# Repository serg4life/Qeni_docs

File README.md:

# Qeni — ESP32-S3 Wearable
Qeni is a custom wearable device based on the ESP32-S3,
designed and developed as a complete electronic product.

The project covers the complete hardware development process,
from system architecture and component selection to PCB and
mechanical design, manufacturing and validation.

## Manufactured prototype

## System Architecture

### High level organization

### Power management

### ESP32 and QSPI memory

### Peripherals

Brief explanation of the main subsystems...

## The PCB design
The PCB design has 4 layers in order to have enough grounding, layer 2 and 3 are solid ground planes. The stack up has been modified to meet the assembler requiremts as well as a proper width and spacing for differential traces. 

### Considerations
- The type and size of the vias have been chosed for a cheap manufacturing
- Components without Pb have been selected in order to meet EU requirements and RoHS
- Most components have been placed on top side for mechanic reasons
- QSPI and SPI traces need controlled length to meet timing requirements
- USB-C and RF traces are impedance-controlled through their width and spacing
- Layers 2 and 3 provide return paths for high-speed signals, reducing unwanted emissions and crosstalk between adjacent traces
- Ground vias are placed near high-speed signal vias to maintain a continuous return path when signals transition between layers

### Layer 1

### Layer 2

### Layer 3

### Layer 4

### PCB renders

## Main Components

- ESP32-S3
- AMOLED display
- Touch controller
- Switch
- IMU
- Speaker
- Microphone
- Audio driver
- Li-Po battery management ICs
- Power management ICs (charging and safety)

### Component Selection

Components were selected considering:

- Electrical requirements
- Availability and lifecycle
- Cost
- Package constraints
- Manufacturing requirements
- Applicable certifications/regulations
- Available support for software development

## Technologies

`ESP32-S3` `ESP-IDF` `C` `KiCad` `Fusion 360` `PCB Design`
`Embedded Systems` `Electronics` `Hardware Validation`

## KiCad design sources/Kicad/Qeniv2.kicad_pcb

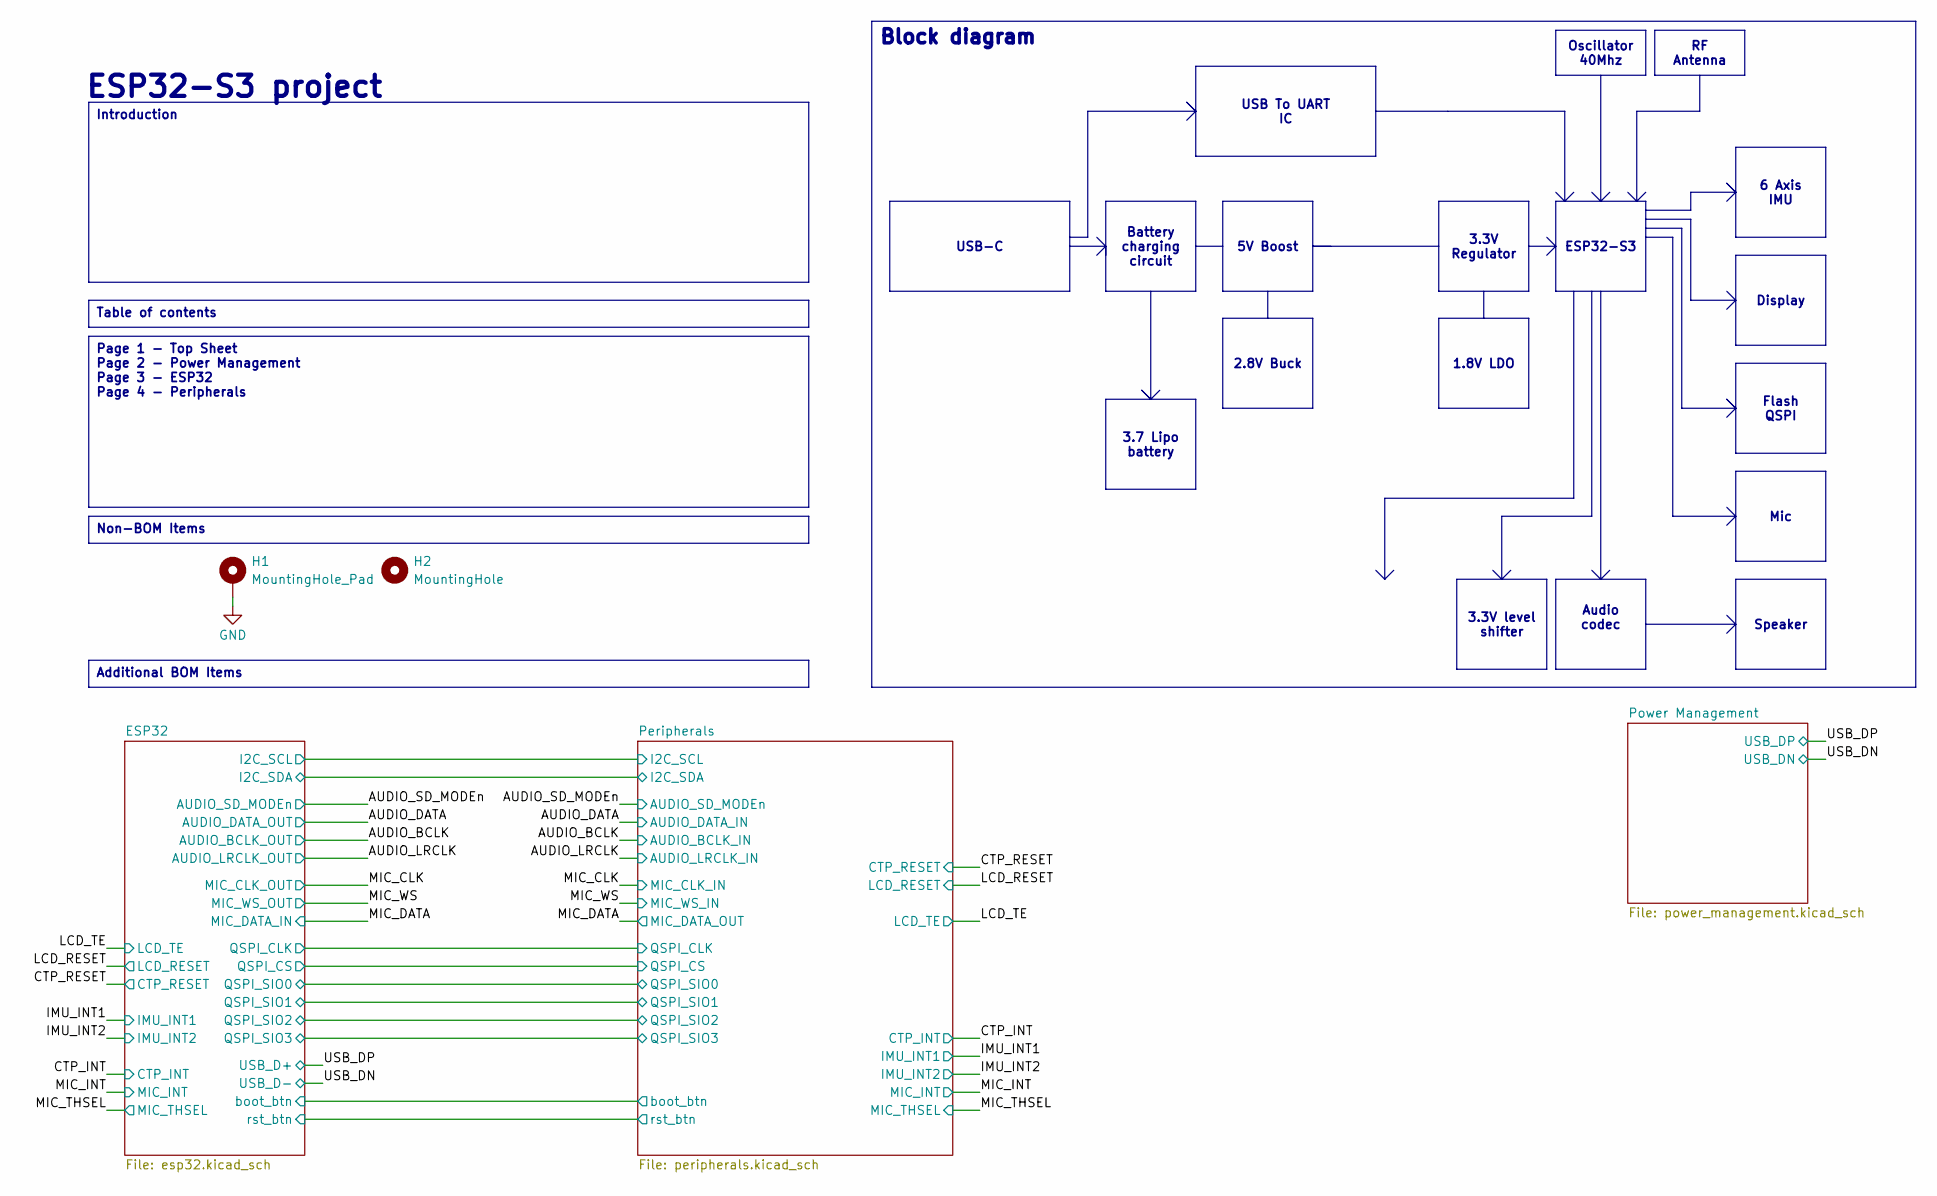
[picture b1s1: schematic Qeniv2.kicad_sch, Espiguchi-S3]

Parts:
H1: MountingHole_Pad; MountingHole_2.2mm_M2_ISO14580_Pad
H2: MountingHole; MountingHole_2.2mm_M2_ISO7380

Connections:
GND: H1.1; also elsewhere on the board

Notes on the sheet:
ESP32-S3 project
3.3V level shifter
RF Antenna
2.8V Buck
Additional BOM Items
Display
USB-C
6 Axis IMU
Battery charging circuit
Block diagram
Page 1 - Top Sheet Page 2 - Power Management Page 3 - ESP32 Page 4 - Peripherals
Table of contents
Introduction
Mic
1.8V LDO
ESP32-S3
Oscillator 40Mhz
5V Boost
3.3V Regulator
USB To UART IC
Audio codec
3.7 Lipo battery
Non-BOM Items
Flash QSPI
Speaker

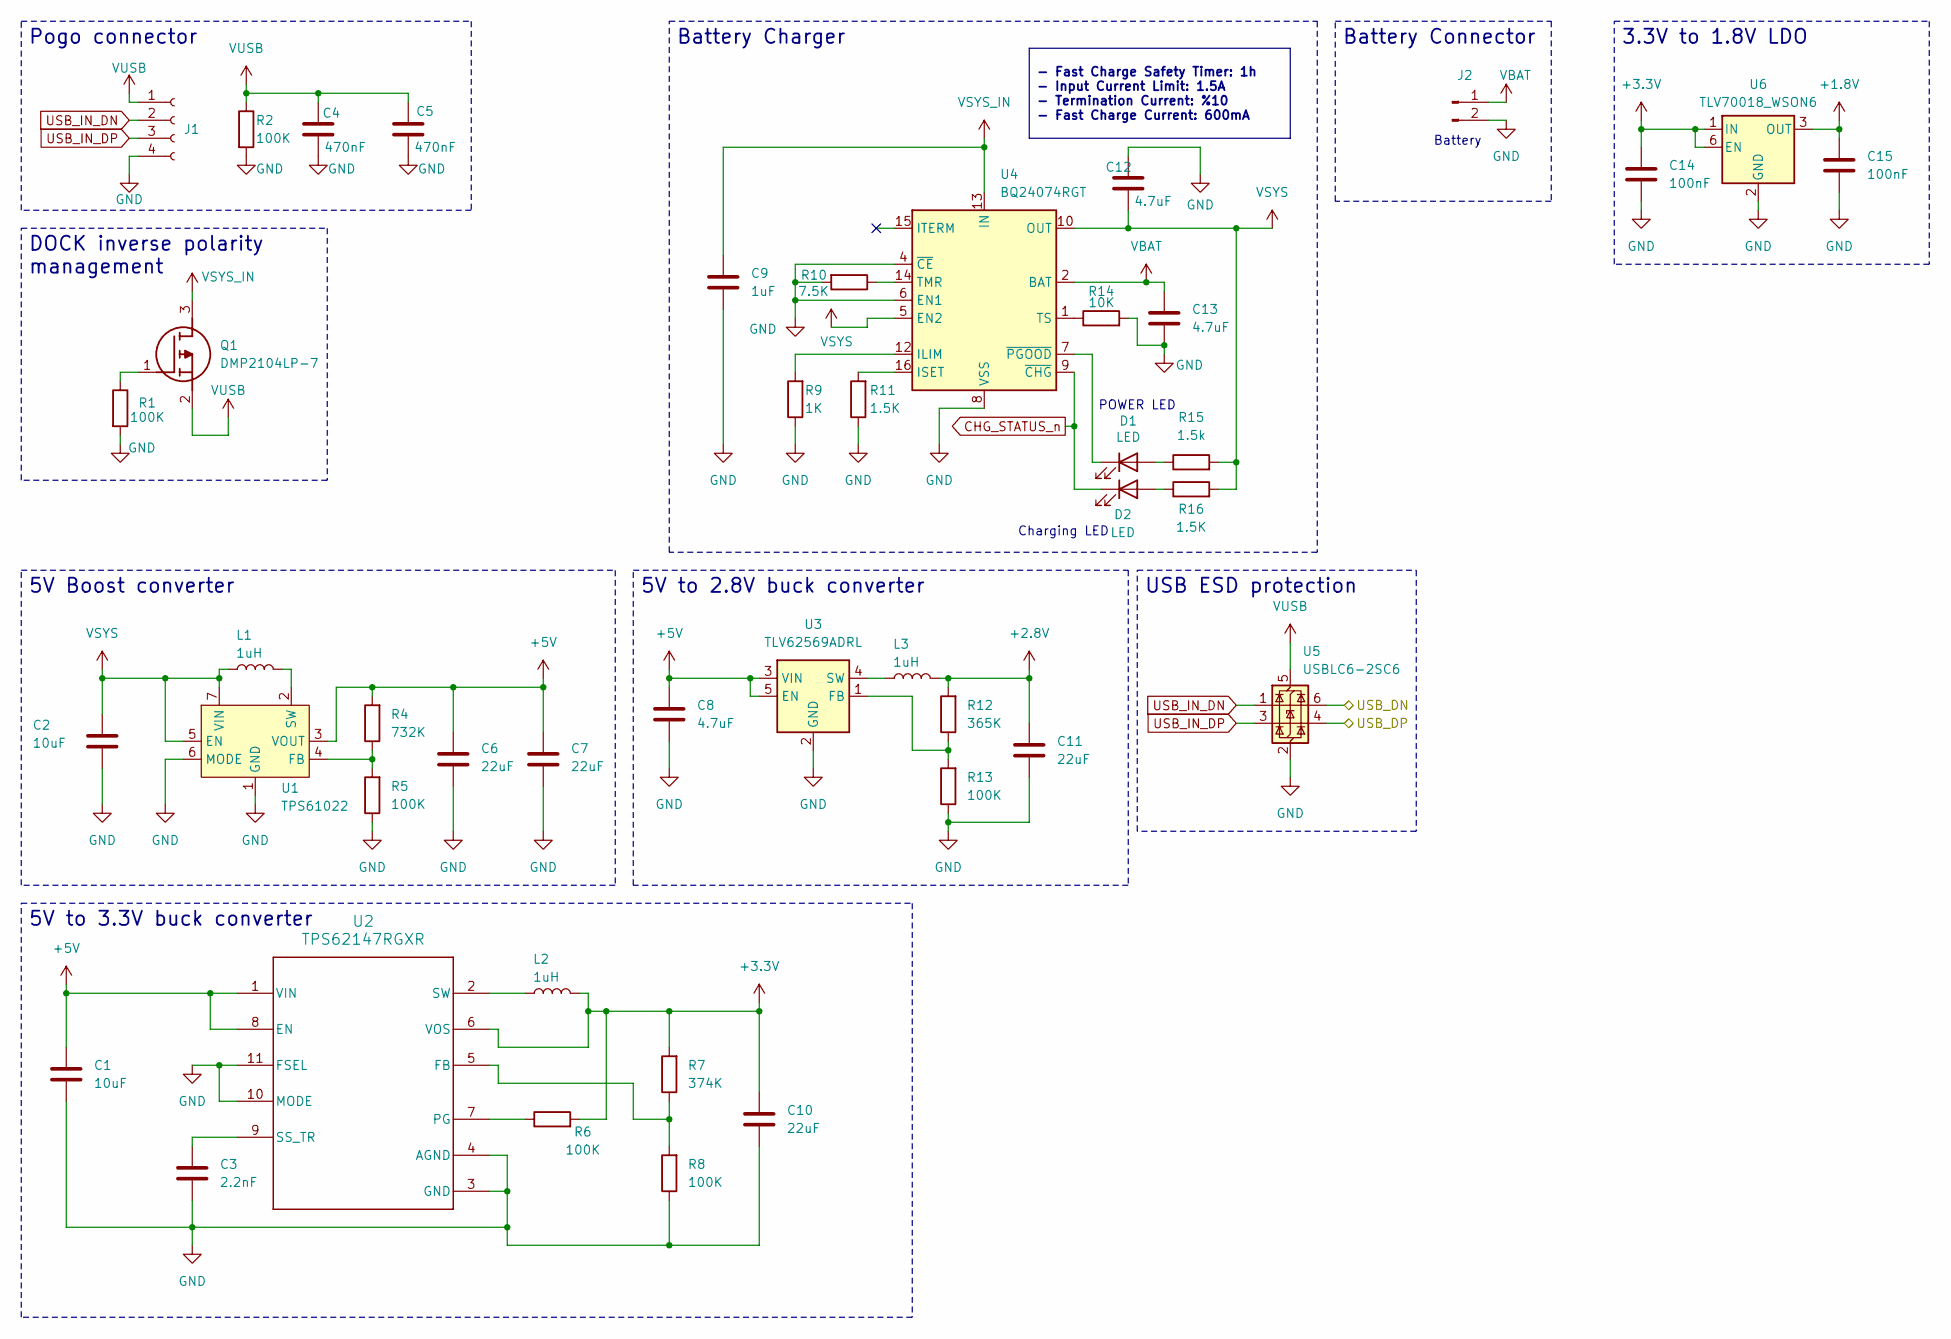
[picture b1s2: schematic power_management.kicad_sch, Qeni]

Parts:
C1: 10uF; C_0603_1608Metric; Part Number C0603C106M9PACTU
C2: 10uF; C_0805_2012Metric; Part Number C0805C106K8PACTU
C3: 2.2nF; C_0402_1005Metric; Part Number GRM155R71E222KA01D
C4, C5: 470nF; C_0201_0603Metric
C6, C7: 22uF; C_0805_2012Metric_Pad1.18x1.45mm_HandSolder; Part Number MSASL219LB5226MTNA01
C8: 4.7uF; C_0603_1608Metric; Part Number C1608X7S1A475K080AC
C9: 1uF; C_0201_0603Metric
C10, C11: 22uF; C_0603_1608Metric; Part Number GRM188R60J226MEA0D
C12, C13: 4.7uF; C_0201_0603Metric
C14: 100nF; C_0201_0603Metric; Part Number GRM155R71C104KA88D
C15: 100nF; C_0201_0603Metric; Part Number C0603X5R1A104K030BC
D1, D2: LED; LED_0201_0603Metric
J1: Conn_01x02_Socket; pogo_pads_1x4
J2: Conn_01x02_Pin; soldered
L1: 1uH; L_Coilcraft_XxL4020; Part Number XFL4020-102MEB
L2: 1uH; INDC2012X100N; Part Number 74479276210C
L3: 1uH; INDC3030X200N; Part Number 74438336010HT
Q1: DMP2104LP-7; DMP2104LP7; Mouser Part Number 621-DMP2104LP-7
R1, R2: 100K; R_0201_0603Metric
R4: 732K; R_0402_1005Metric_Pad0.72x0.64mm_HandSolder; Part Number CRCW0402732KFKED
R5: 100K; R_0402_1005Metric_Pad0.72x0.64mm_HandSolder; Part Number CRCW0402100KFKED
R6, R8, R13: 100K; R_0402_1005Metric; Part Number CRCW0402100KFKED
R7: 374K; R_0402_1005Metric; Part Number CRCW0402374KFKED
R9: 1K; R_0201_0603Metric
R10: 7.5K; R_0201_0603Metric
R11, R16: 1.5K; R_0201_0603Metric
R12: 365K; R_0402_1005Metric; Part Number CRCW0402365KFKED
R14: 10K; R_0201_0603Metric
R15: 1.5k; R_0201_0603Metric
U1: TPS61022; Texas_RWU0007A_VQFN-7_2x2mm_P0.5mm; Part Number TPS61022RWUR
U2: TPS62147RGXR; RGX0011A
U3: TLV62569ADRL; SOT-563; Part Number TLV62569ADRLR
U4: BQ24074RGT; VQFN-16-1EP_3x3mm_P0.5mm_EP1.6x1.6mm
U5: USBLC6-2SC6; SOT-23-6
U6: TLV70018_WSON6; WSON-6_1.5x1.5mm_P0.5mm; Part Number TLV70018DDCR

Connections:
+1.8V: C15.1, U6.3 (OUT); also elsewhere on the board
+2.8V: C11.1, L3.2, R12.2; also elsewhere on the board
+3.3V: C10.1, C14.1, L2.2, R6.2, R7.2, U2.6 (VOS), U6.1 (IN), U6.6 (EN); also elsewhere on the board
+5V: C1.1, C6.1, C7.1, C8.1, R4.2, U1.3 (VOUT), U2.1 (VIN), U2.8 (EN), U3.3 (VIN), U3.5 (EN); also elsewhere on the board
/USB_DN: U5.6 (I/O1); also elsewhere on the board
/USB_DP: U5.4 (I/O2); also elsewhere on the board
CHG_STATUS_n: D2.1 (K), U4.9 (~CHG); also elsewhere on the board
GND: C1.2, C2.2, C3.2, C4.2, C5.2, C6.2, C7.2, C8.2, C9.2, C10.2, C11.2, C12.1, C13.2, C14.2, C15.2, J1.4, J2.2, R1.2, R2.2, R5.1, R8.1, R9.1, R10.2, R11.1, R13.1, R14.2, U1.1 (GND), U1.6 (MODE), U2.3 (GND), U2.4 (AGND), U2.10 (MODE), U2.11 (FSEL), U3.2 (GND), U4.4 (~CE), U4.6 (EN1), U4.8 (VSS), U4.17 (VSS), U5.2 (GND), U6.2 (GND); also elsewhere on the board
unnamed: D1.2 (A), R15.1
unnamed: D1.1 (K), U4.7 (~PGOOD)
unnamed: D2.2 (A), R16.1
unnamed: Q1.1 (G), R1.1
unnamed: R4.1, R5.2, U1.4 (FB)
unnamed: L1.2, U1.2 (SW)
unnamed: R7.1, R8.2, U2.5 (FB)
unnamed: R6.1, U2.7 (PG)
unnamed: C3.1, U2.9 (SS_TR)
unnamed: L2.1, U2.2 (SW)
unnamed: R12.1, R13.2, U3.1 (FB)
unnamed: L3.1, U3.4 (SW)
unnamed: R9.2, U4.12 (ILIM)
unnamed: R11.2, U4.16 (ISET)
unnamed: R10.1, U4.14 (TMR)
unnamed: R14.1, U4.1 (TS)
USB_IN_DN: J1.2, U5.1 (I/O1)
USB_IN_DP: J1.3, U5.3 (I/O2)
VBAT: C13.1, J2.1, U4.2 (BAT), U4.3 (BAT)
VSYS: C2.1, C12.2, L1.1, R15.2, R16.2, U1.5 (EN), U1.7 (VIN), U4.5 (EN2), U4.10 (OUT), U4.11 (OUT)
VSYS_IN: C9.1, Q1.3 (D), U4.13 (IN)
VUSB: C4.1, C5.1, J1.1, Q1.2 (S), R2.1, U5.5 (VBUS)

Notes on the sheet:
POWER LED
Charging LED
Battery
USB ESD protection
Pogo connector
5V Boost converter
3.3V to 1.8V LDO
5V to 3.3V buck converter
Battery Charger
- Fast Charge Safety Timer: 1h - Input Current Limit: 1.5A - Termination Current: %10 - Fast Charge Current: 600mA
DOCK inverse polarity management
Battery Connector
5V to 2.8V buck converter

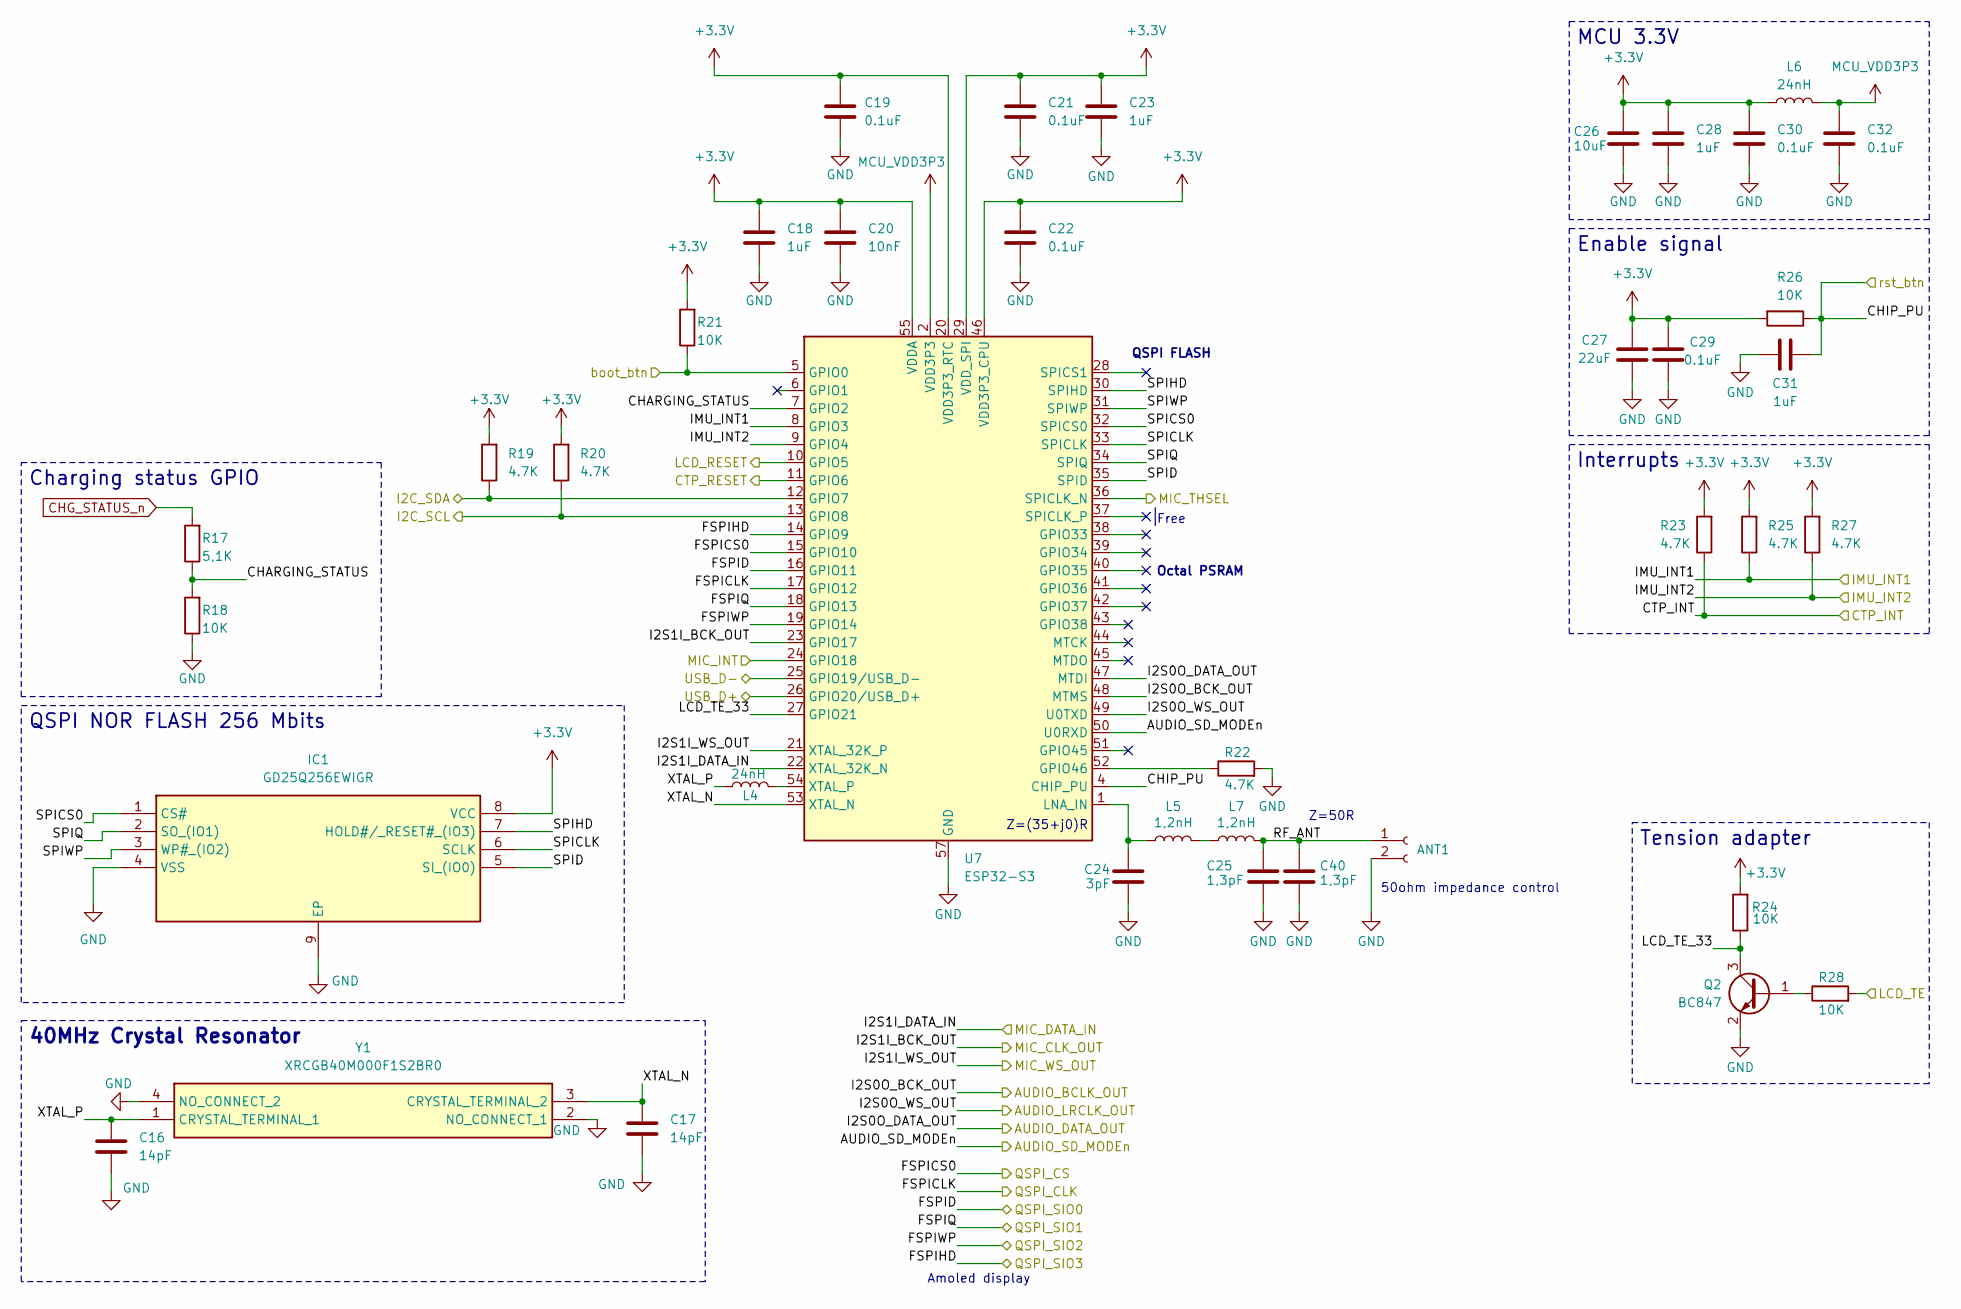
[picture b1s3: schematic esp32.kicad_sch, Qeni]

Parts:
ANT1: Conn_01x02_Socket; Texas_SWRA117D_2.4GHz_Left
C16, C17: 14pF; C_0201_0603Metric
C18, C23, C28, C31: 1uF; C_0201_0603Metric
C19, C21, C22, C29, C30, C32: 0.1uF; C_0201_0603Metric
C20: 10nF; C_0201_0603Metric
C24: 3pF; C_0201_0603Metric
C25, C40: 1,3pF; C_0201_0603Metric
C26: 10uF; C_0603_1608Metric
C27: 22uF; C_0805_2012Metric
IC1: GD25Q256EWIGR; SON127P500X600X80-9N-D; Manufacturer_Part_Number GD25Q256EWIGR
L4, L6: 24nH; L_0201_0603Metric
L5, L7: 1,2nH; L_0201_0603Metric
Q2: BC847; SOT-23
R17: 5,1K; R_0201_0603Metric
R18, R21, R24, R26, R28: 10K; R_0201_0603Metric
R19, R20, R22, R23, R25, R27: 4.7K; R_0201_0603Metric
U7: ESP32-S3; QFN-56-1EP_7x7mm_P0.4mm_EP4x4mm
Y1: XRCGB40M000F1S2BR0; Manufacturer_Part_Number XRCGB40M000F1S2BR0

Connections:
+3.3V: C18.1, C19.2, C20.1, C21.2, C22.2, C23.1, C26.2, C27.2, C28.2, C29.1, C30.2, IC1.8 (VCC), L6.1, R19.2, R20.2, R21.2, R23.2, R24.2, R25.2, R26.2, R27.2, U7.20 (VDD3P3_RTC), U7.29 (VDD_SPI), U7.46 (VDD3P3_CPU), U7.55 (VDDA), U7.56 (VDDA); also elsewhere on the board
/AUDIO_BCLK: U7.48 (MTMS); also elsewhere on the board
/AUDIO_DATA: U7.47 (MTDI); also elsewhere on the board
/AUDIO_LRCLK: U7.49 (U0TXD); also elsewhere on the board
/AUDIO_SD_MODEn: U7.50 (U0RXD); also elsewhere on the board
/CTP_INT: R23.1; also elsewhere on the board
/CTP_RESET: U7.11 (GPIO6); also elsewhere on the board
/ESP32/CHARGING_STATUS: R17.1, R18.2, U7.7 (GPIO2)
/ESP32/CHIP_PU: C31.2, R26.1, U7.4 (CHIP_PU); also elsewhere on the board
/ESP32/FSPICLK: U7.17 (GPIO12); also elsewhere on the board
/ESP32/FSPICS0: U7.15 (GPIO10); also elsewhere on the board
/ESP32/FSPID: U7.16 (GPIO11); also elsewhere on the board
/ESP32/FSPIHD: U7.14 (GPIO9); also elsewhere on the board
/ESP32/FSPIQ: U7.18 (GPIO13); also elsewhere on the board
/ESP32/FSPIWP: U7.19 (GPIO14); also elsewhere on the board
/ESP32/LCD_TE_33: Q2.3 (C), R24.1, U7.27 (GPIO21)
/ESP32/RF_ANT: ANT1.1, C25.1, C40.1, L7.2
/ESP32/SPICLK: IC1.6 (SCLK), U7.33 (SPICLK)
/ESP32/SPICS0: IC1.1 (CS#), U7.32 (SPICS0)
/ESP32/SPID: IC1.5 (SI_(IO0)), U7.35 (SPID)
/ESP32/SPIHD: IC1.7 (HOLD#/_RESET#_(IO3)), U7.30 (SPIHD)
/ESP32/SPIQ: IC1.2 (SO_(IO1)), U7.34 (SPIQ)
/ESP32/SPIWP: IC1.3 (WP#_(IO2)), U7.31 (SPIWP)
/ESP32/XTAL_N: C17.1, U7.53 (XTAL_N), Y1.3 (CRYSTAL_TERMINAL_2)
/ESP32/XTAL_P: C16.1, L4.1, Y1.1 (CRYSTAL_TERMINAL_1)
/ESP32/boot_btn: R21.1, U7.5 (GPIO0); also elsewhere on the board
/IMU_INT1: R25.1, U7.8 (GPIO3); also elsewhere on the board
/IMU_INT2: R27.1, U7.9 (GPIO4); also elsewhere on the board
/LCD_RESET: U7.10 (GPIO5); also elsewhere on the board
/LCD_TE: R28.2; also elsewhere on the board
/MIC_CLK: U7.23 (GPIO17); also elsewhere on the board
/MIC_DATA: U7.22 (XTAL_32K_N); also elsewhere on the board
/MIC_INT: U7.24 (GPIO18); also elsewhere on the board
/MIC_THSEL: U7.36 (SPICLK_N); also elsewhere on the board
/MIC_WS: U7.21 (XTAL_32K_P); also elsewhere on the board
/Peripherals/CTP_SCL: R20.1, U7.13 (GPIO8); also elsewhere on the board
/Peripherals/CTP_SDA: R19.1, U7.12 (GPIO7); also elsewhere on the board
/USB_DN: U7.25 (GPIO19/USB_D-); also elsewhere on the board
/USB_DP: U7.26 (GPIO20/USB_D+); also elsewhere on the board
CHG_STATUS_n: R17.2; also elsewhere on the board
GND: ANT1.2, C16.2, C17.2, C18.2, C19.1, C20.2, C21.1, C22.1, C23.2, C24.2, C25.2, C26.1, C27.1, C28.1, C29.2, C30.1, C31.1, C32.1, C40.2, IC1.4 (VSS), IC1.9 (EP), Q2.2 (E), R18.1, R22.2, U7.57 (GND), Y1.2 (NO_CONNECT_1), Y1.4 (NO_CONNECT_2); also elsewhere on the board
MCU_VDD3P3: C32.2, L6.2, U7.2 (VDD3P3), U7.3 (VDD3P3)
unnamed: L5.2, L7.1
unnamed: Q2.1 (B), R28.1
unnamed: R22.1, U7.52 (GPIO46)
unnamed: C24.1, L5.1, U7.1 (LNA_IN)
unnamed: L4.2, U7.54 (XTAL_P)

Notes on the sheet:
Amoled display
Octal PSRAM
50ohm impedance control
Free
Z=50R
Z=(35+j0)R
QSPI FLASH
40MHz Crystal Resonator
Tension adapter
Enable signal
Interrupts
QSPI NOR FLASH 256 Mbits
Charging status GPIO
MCU 3.3V

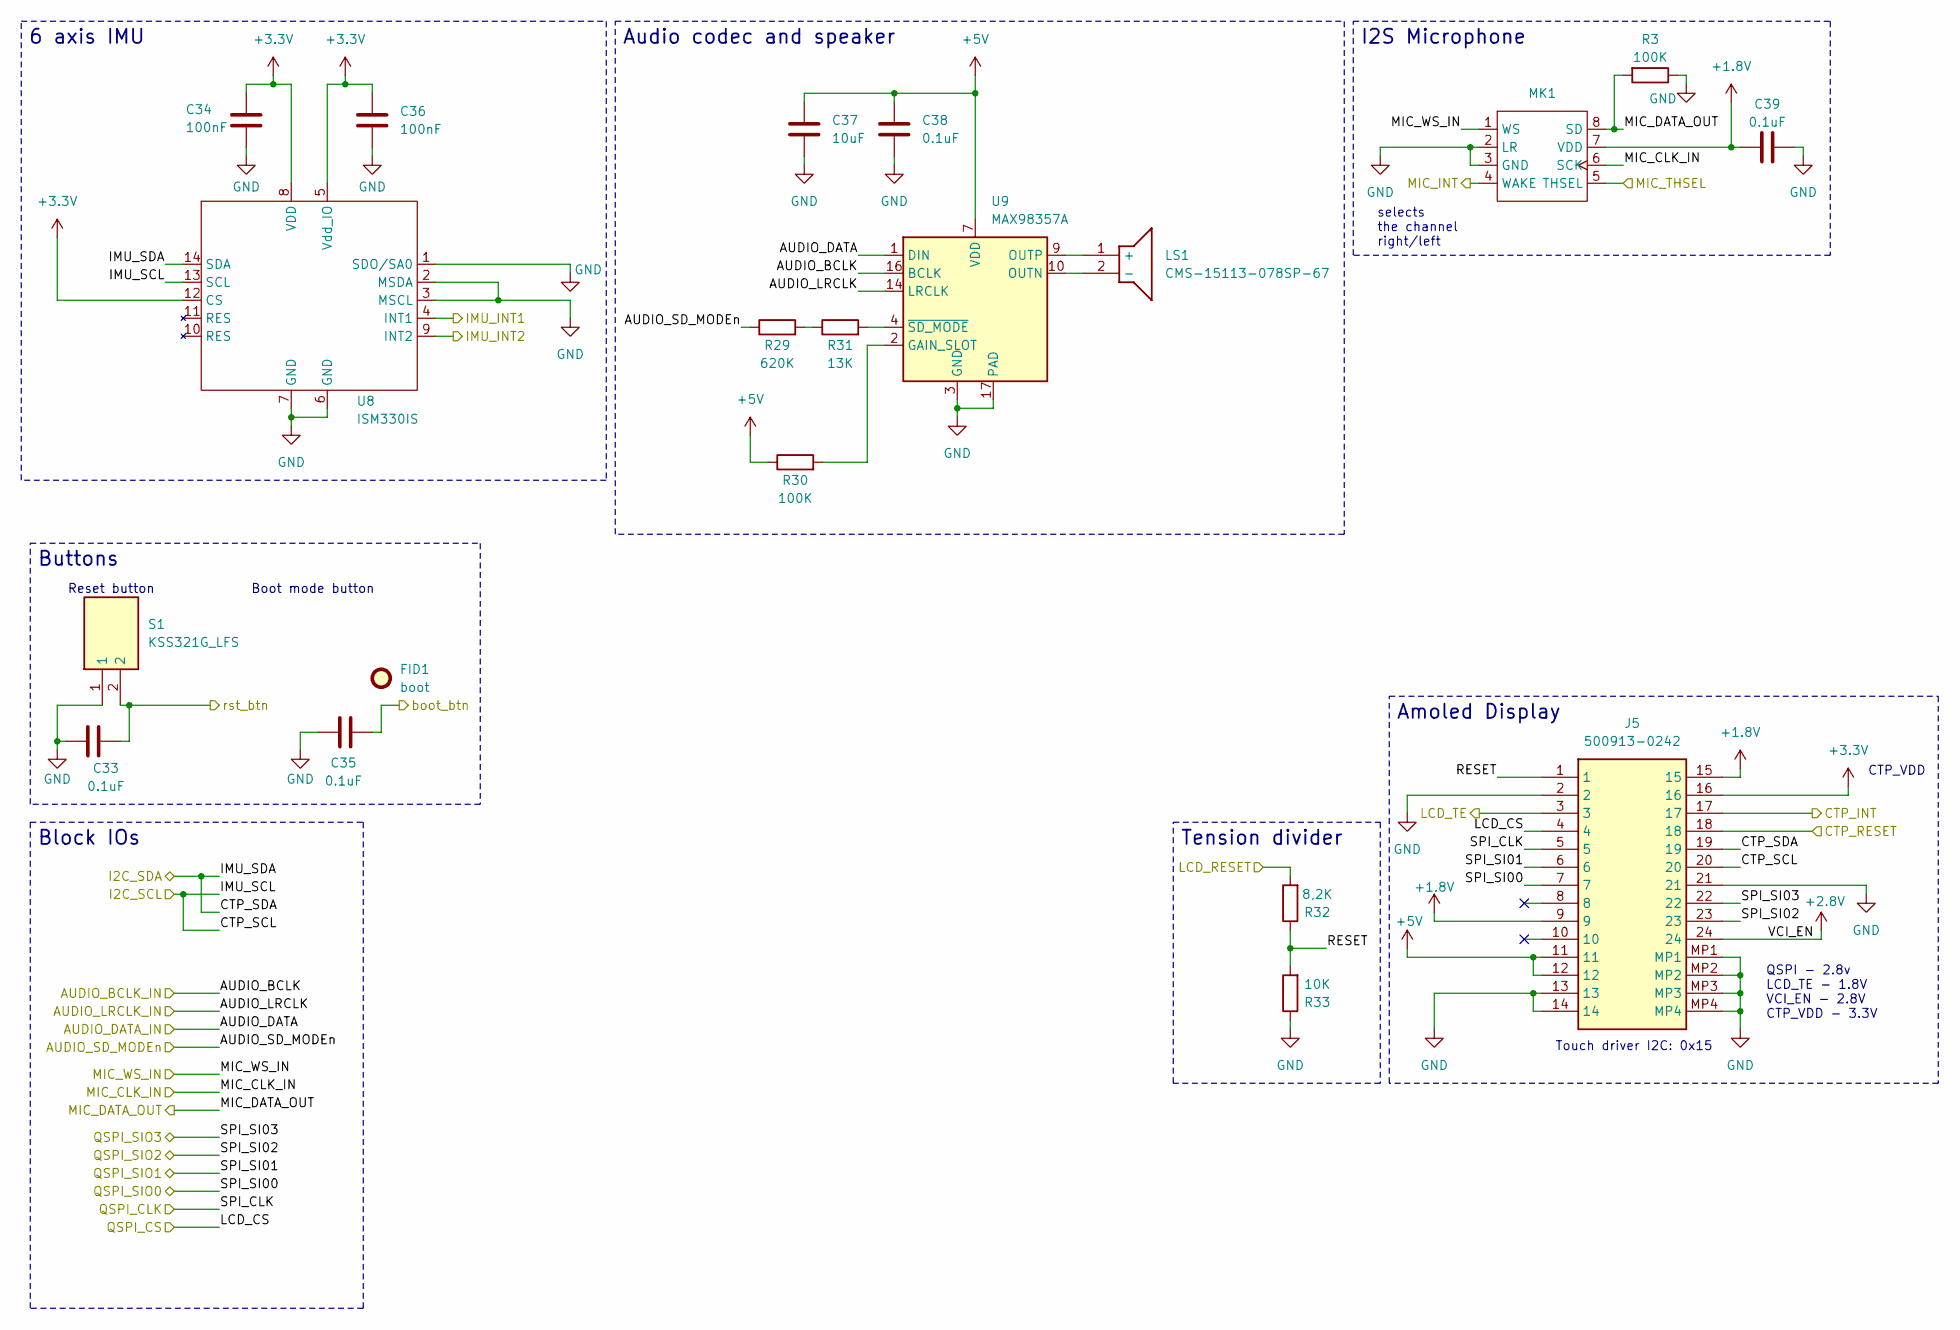
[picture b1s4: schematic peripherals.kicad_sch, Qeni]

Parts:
C33, C35, C38, C39: 0.1uF; C_0201_0603Metric
C34, C36: 100nF; C_0201_0603Metric
C37: 10uF; C_0603_1608Metric
FID1: boot; Fiducial_0.5mm_Mask1mm
J5: 500913-0242; OK-23GF024-04; Mouser Part Number 538-500913-0242
LS1: CMS-15113-078SP-67; Audio pad; Mouser Part Number 490-CMS-15113078SP67
MK1: MMICT5848
R3, R30: 100K; R_0201_0603Metric
R29: 620K; R_0201_0603Metric
R31: 13K; R_0201_0603Metric
R32: 8,2K; R_0201_0603Metric
R33: 10K; R_0201_0603Metric
S1: KSS321G_LFS; KSS321GLFS; Manufacturer_Part_Number KSS321G LFS
U8: ISM330IS
U9: MAX98357A; TQFN-16-1EP_3x3mm_P0.5mm_EP1.23x1.23mm

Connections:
+1.8V: C39.1, J5.9, J5.15, MK1.7 (VDD); also elsewhere on the board
+2.8V: J5.24; also elsewhere on the board
+3.3V: C34.1, C36.1, J5.16, U8.5 (Vdd_IO), U8.8 (VDD), U8.12 (CS); also elsewhere on the board
+5V: C37.1, C38.1, J5.11, J5.12, R30.1, U9.7 (VDD), U9.8 (VDD); also elsewhere on the board
/AUDIO_BCLK: U9.16 (BCLK); also elsewhere on the board
/AUDIO_DATA: U9.1 (DIN); also elsewhere on the board
/AUDIO_LRCLK: U9.14 (LRCLK); also elsewhere on the board
/AUDIO_SD_MODEn: R29.1; also elsewhere on the board
/CTP_INT: J5.17; also elsewhere on the board
/CTP_RESET: J5.18; also elsewhere on the board
/ESP32/CHIP_PU: C33.2, S1.2; also elsewhere on the board
/ESP32/FSPICLK: J5.5; also elsewhere on the board
/ESP32/FSPICS0: J5.4; also elsewhere on the board
/ESP32/FSPID: J5.7; also elsewhere on the board
/ESP32/FSPIHD: J5.22; also elsewhere on the board
/ESP32/FSPIQ: J5.6; also elsewhere on the board
/ESP32/FSPIWP: J5.23; also elsewhere on the board
/ESP32/boot_btn: C35.2; also elsewhere on the board
/IMU_INT1: U8.4 (INT1); also elsewhere on the board
/IMU_INT2: U8.9 (INT2); also elsewhere on the board
/LCD_RESET: R32.2; also elsewhere on the board
/LCD_TE: J5.3; also elsewhere on the board
/MIC_CLK: MK1.6 (SCK); also elsewhere on the board
/MIC_DATA: MK1.8 (SD), R3.2; also elsewhere on the board
/MIC_INT: MK1.4 (WAKE); also elsewhere on the board
/MIC_THSEL: MK1.5 (THSEL); also elsewhere on the board
/MIC_WS: MK1.1 (WS); also elsewhere on the board
/Peripherals/CTP_SCL: J5.20, U8.13 (SCL); also elsewhere on the board
/Peripherals/CTP_SDA: J5.19, U8.14 (SDA); also elsewhere on the board
/Peripherals/RESET: J5.1, R32.1, R33.2
GND: C33.1, C34.2, C35.1, C36.2, C37.2, C38.2, C39.2, J5.2, J5.13, J5.14, J5.21, J5.MP1, J5.MP2, J5.MP3, J5.MP4, MK1.2 (LR), MK1.3 (GND), R3.1, R33.1, S1.1, U8.1 (SDO/SA0), U8.2 (MSDA), U8.3 (MSCL), U8.6 (GND), U8.7 (GND), U9.3 (GND), U9.11 (GND), U9.15 (GND), U9.17 (PAD); also elsewhere on the board
unnamed: LS1.1 (+), U9.9 (OUTP)
unnamed: LS1.2 (-), U9.10 (OUTN)
unnamed: R29.2, R31.1
unnamed: R30.2, U9.2 (GAIN_SLOT)
unnamed: R31.2, U9.4 (~SD_MODE)

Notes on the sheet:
selects the channel right/left
Touch driver I2C: 0x15
CTP_VDD
Boot mode button
Reset button
QSPI - 2.8v LCD_TE - 1.8V VCI_EN - 2.8V CTP_VDD - 3.3V
Buttons
Amoled Display
6 axis IMU
Tension divider
Block IOs
I2S Microphone
Audio codec and speaker

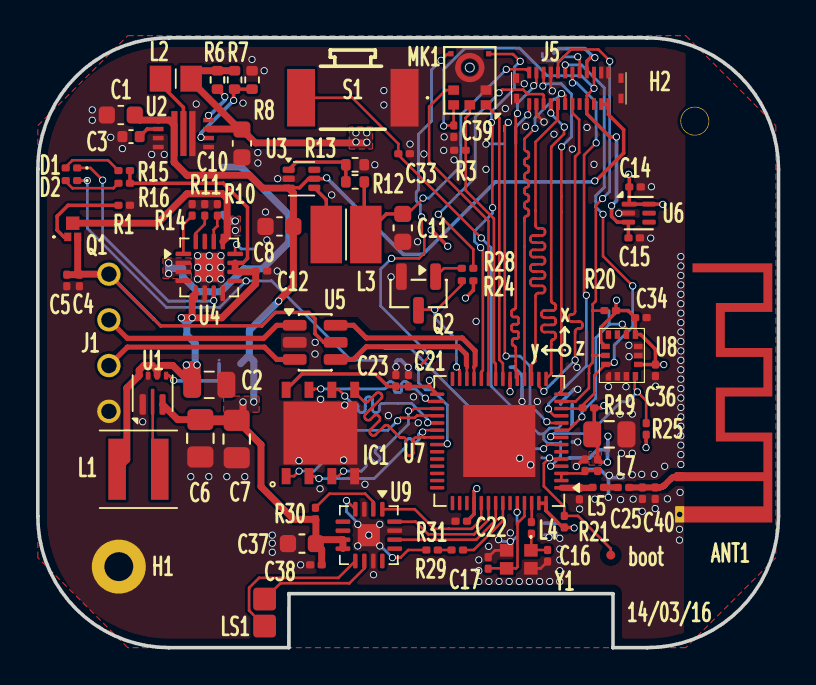
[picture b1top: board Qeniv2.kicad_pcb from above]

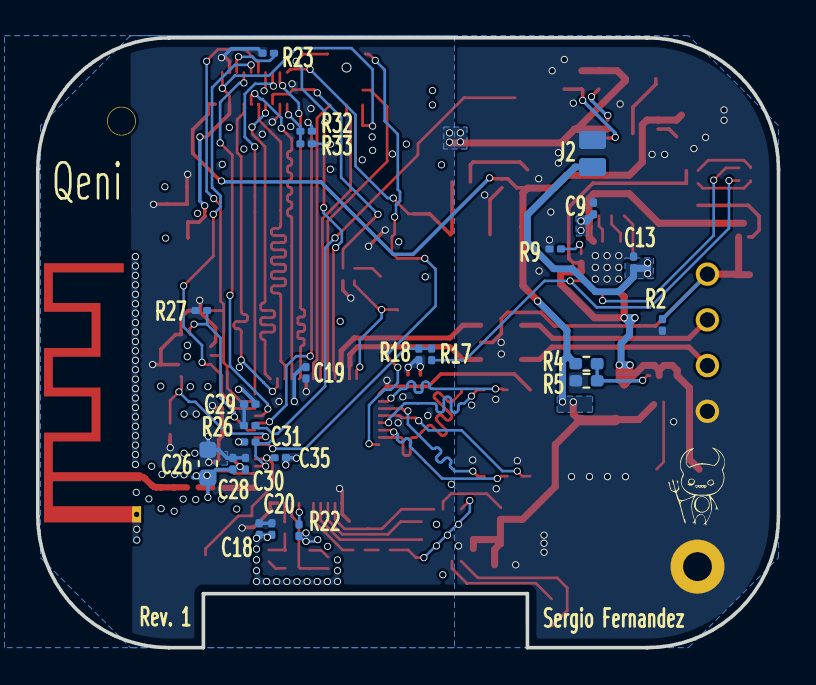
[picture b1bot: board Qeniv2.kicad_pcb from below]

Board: 4 copper layers, 41.1 x 33.9 mm, 105 parts (24 on the bottom side), 78 nets.
